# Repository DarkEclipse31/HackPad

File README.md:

# Orpheuspad

# BOM:
- 7x Cherry MX switches
- 1x EC11 Encoder
- 1x PCB
- 1x 0.96 inch 128x64 OLED
- 4x M3 12mm Bolts in BOM

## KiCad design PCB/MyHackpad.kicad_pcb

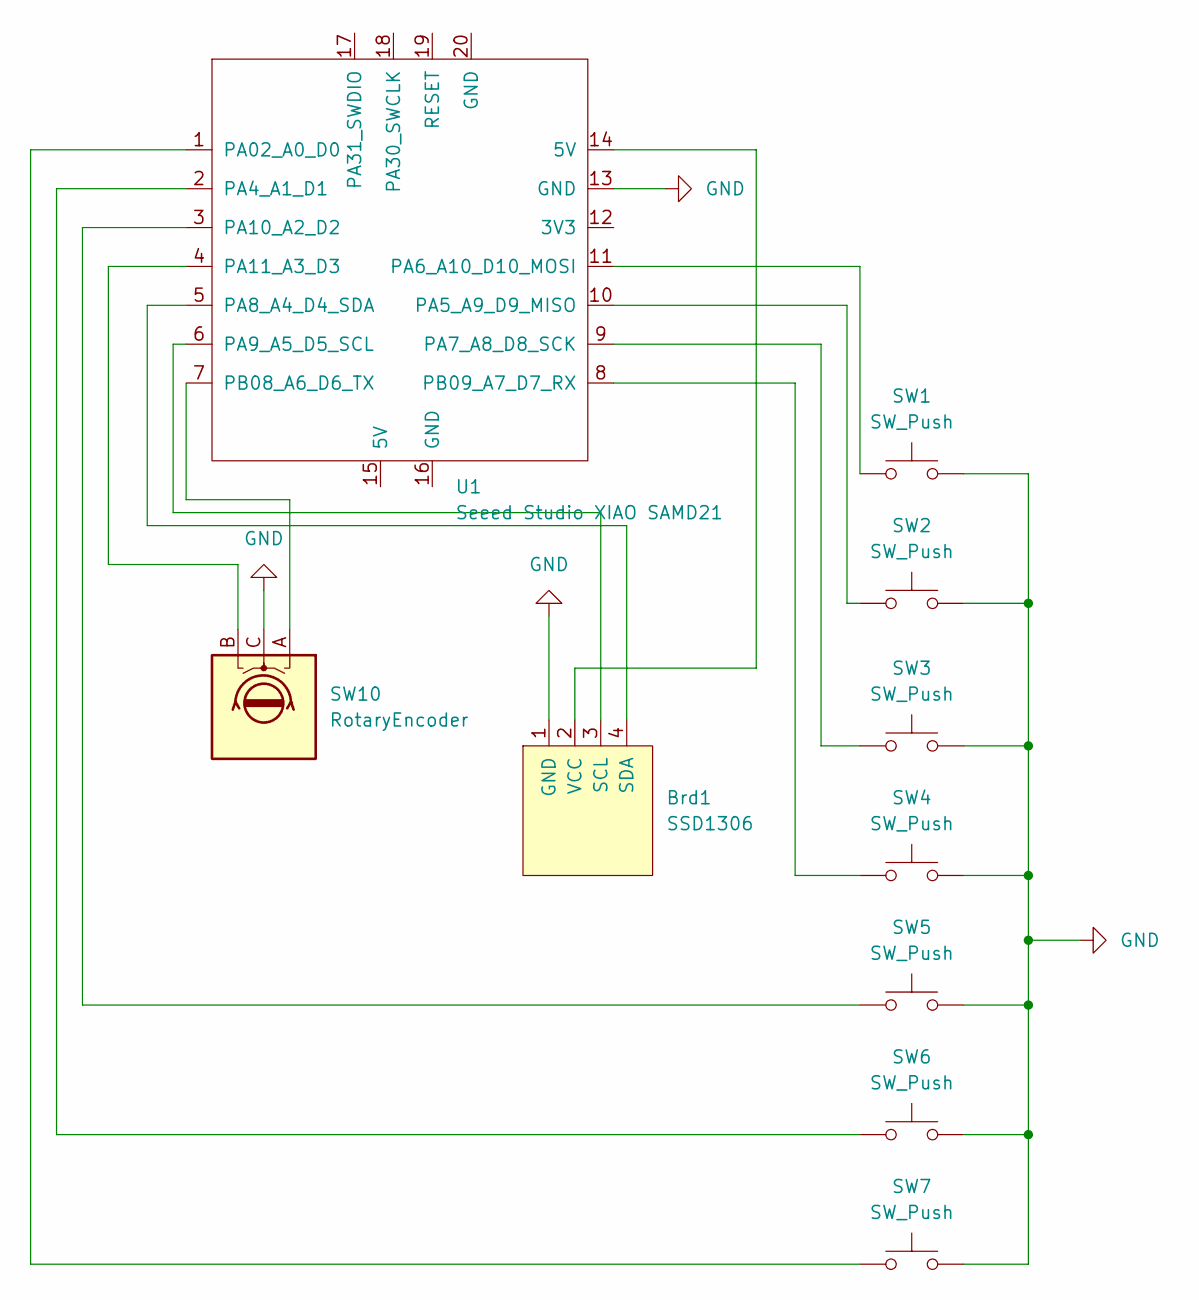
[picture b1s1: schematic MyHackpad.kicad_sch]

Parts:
Brd1: SSD1306; 128x64OLED
SW1, SW2, SW3, SW4, SW5, SW6, SW7: SW_Push; SW_Cherry_MX_1.00u_PCB
SW10: RotaryEncoder; RotaryEncoder_Alps_EC11E-Switch_Vertical_H20mm
U1: Seeed Studio XIAO SAMD21; XIAO-Generic-Thruhole-14P-2.54-21X17.8MM

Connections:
GND: Brd1.1 (GND), SW1.2, SW2.2, SW3.2, SW4.2, SW5.2, SW6.2, SW7.2, SW10.C, U1.13 (GND)
unnamed: Brd1.3 (SCL), U1.6 (PA9_A5_D5_SCL)
unnamed: Brd1.4 (SDA), U1.5 (PA8_A4_D4_SDA)
unnamed: Brd1.2 (VCC), U1.14 (5V)
unnamed: SW7.1, U1.1 (PA02_A0_D0)
unnamed: SW6.1, U1.2 (PA4_A1_D1)
unnamed: SW2.1, U1.10 (PA5_A9_D9_MISO)
unnamed: SW1.1, U1.11 (PA6_A10_D10_MOSI)
unnamed: SW3.1, U1.9 (PA7_A8_D8_SCK)
unnamed: SW5.1, U1.3 (PA10_A2_D2)
unnamed: SW10.B, U1.4 (PA11_A3_D3)
unnamed: SW10.A, U1.7 (PB08_A6_D6_TX)
unnamed: SW4.1, U1.8 (PB09_A7_D7_RX)

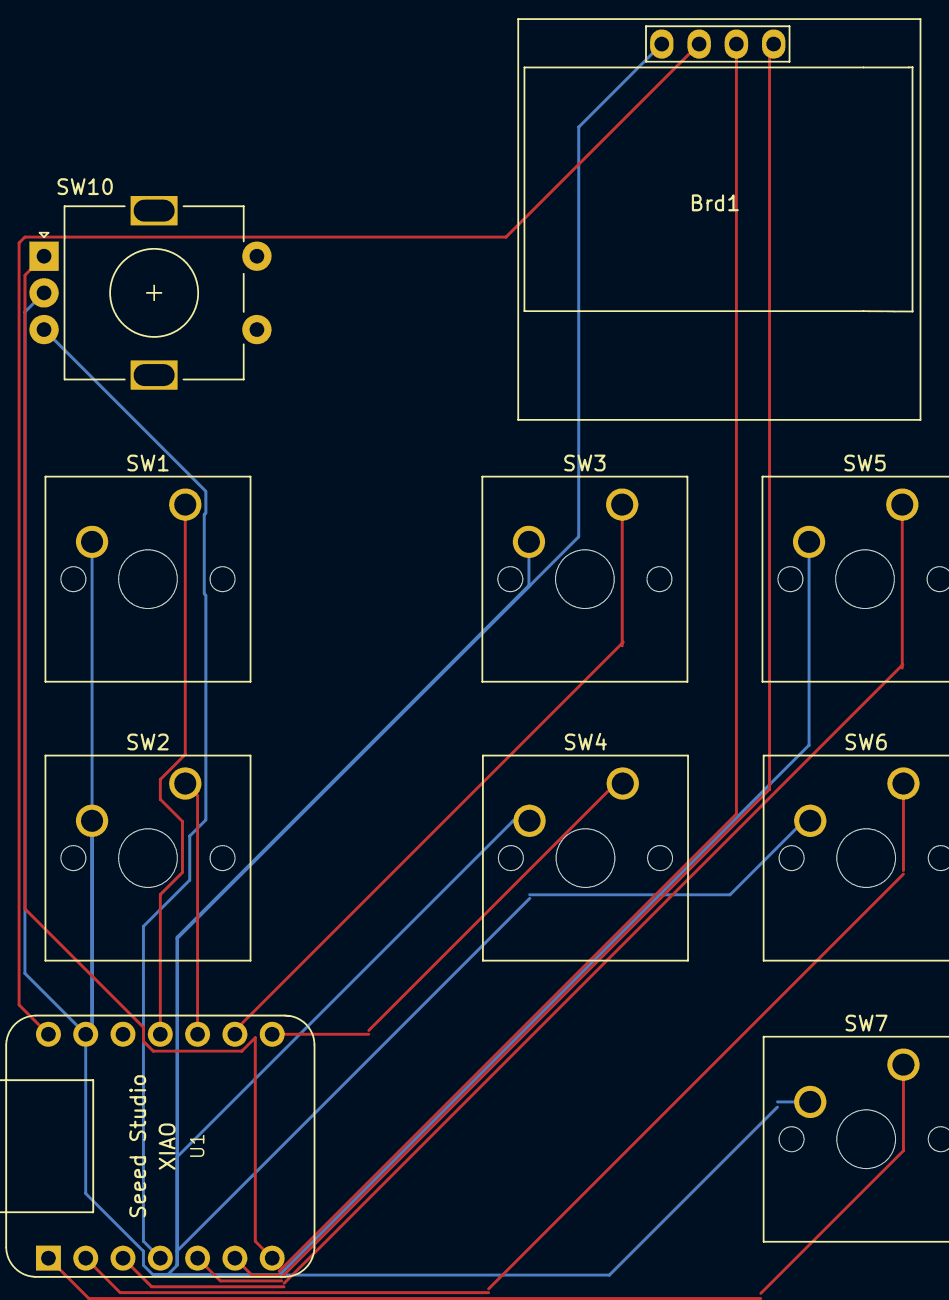
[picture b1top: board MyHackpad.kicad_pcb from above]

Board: 2 copper layers, 10 parts (0 on the bottom side), 13 nets.

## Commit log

2024-10-06 Adding mcu
2024-10-14 CAD + PCB
2024-10-14 README.md
